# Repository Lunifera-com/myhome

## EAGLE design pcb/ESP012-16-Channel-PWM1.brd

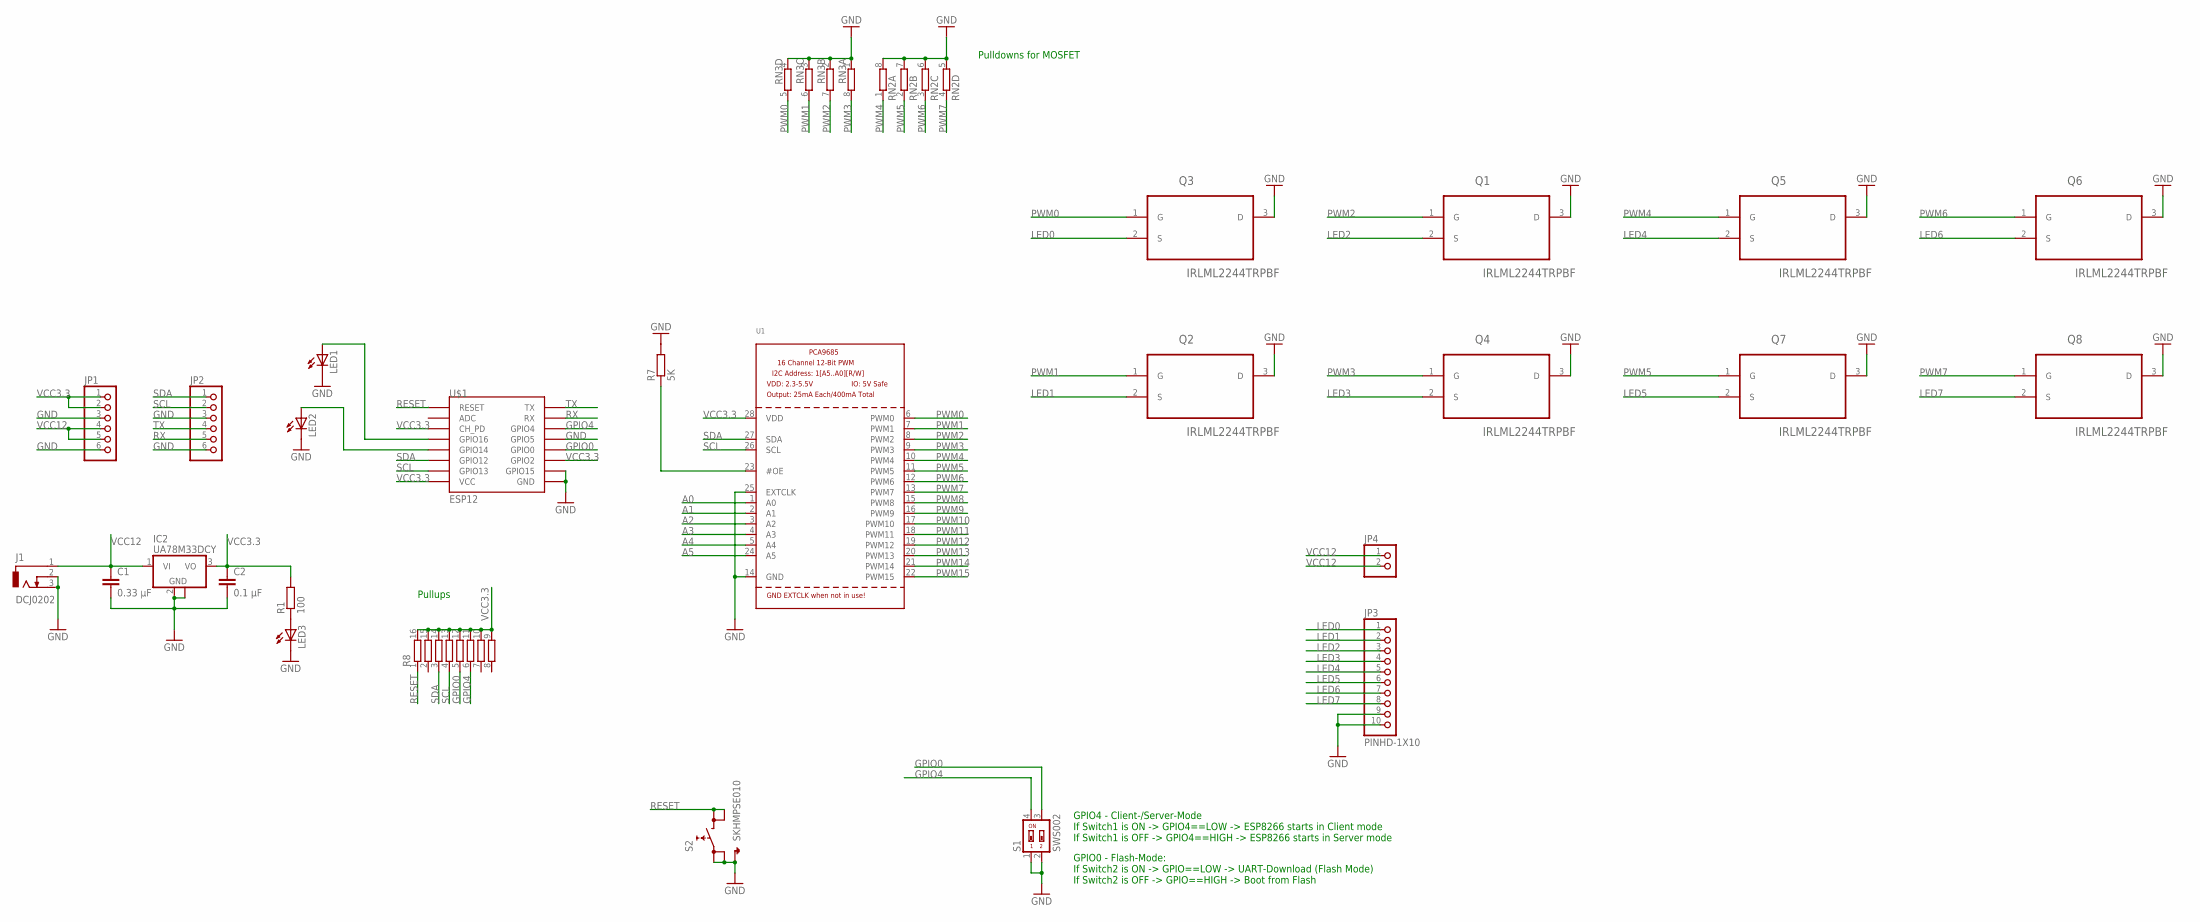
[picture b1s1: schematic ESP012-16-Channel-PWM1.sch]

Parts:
C1: 0.33 µF; C025-024X044
C2: 0.1 µF; C025-024X044
IC2: UA78M33DCY; SOT223
J1: DCJ0202
JP1, JP2: PINHD-1X6; 1X06
JP3: PINHD-1X10; 1X10-BIG
JP4: PINHD-1X2; 1X02
LED1, LED2, LED3: LEDCHIP-LED0805; CHIP-LED0805
Q1, Q2, Q3, Q4, Q5, Q6, Q7, Q8: IRLML2244TRPBF; SOT95P237X112-3N
R1: 100; MINI_MELF-0207R
R7: 5K; MINI_MELF-0207R
R8: 2QSP16-8; 2QSP16
RN2, RN3: 4R-NEXBS8V; EXBS8V
S1: SWS002; SMS-002
S2: SKHMPSE010; SKHMPXE010
U1: PCA9685; TSSOP28
U$1: ESP12

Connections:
A0: U1.1 (A0)
A1: U1.2 (A1)
A2: U1.3 (A2)
A3: U1.4 (A3)
A4: U1.5 (A4)
A5: U1.24 (A5)
GND: C1.2, C2.2, IC2.2 (GND), IC2.4 (GND), J1.2, J1.3, JP1.3, JP1.6, JP2.3, JP2.6, JP3.9, JP3.10, LED1.C, LED2.C, LED3.C, Q1.3 (D), Q2.3 (D), Q3.3 (D), Q4.3 (D), Q5.3 (D), Q6.3 (D), Q7.3 (D), Q8.3 (D), R7.2, RN2.5 (2), RN2.6 (2), RN2.7 (2), RN2.8 (2), RN3.1, RN3.2 (1), RN3.3 (1), RN3.4 (1), S1.1, S1.2, S2.1 (1.1), S2.2 (1.2), S2.5 (SH), U1.14 (GND), U1.25 (EXTCLK), U$1.GND, U$1.GPIO5, U$1.GPIO15
GPIO0: R8.5, S1.3, U$1.GPIO0
GPIO4: R8.6, S1.4, U$1.GPIO4
LED0: JP3.1, Q3.2 (S)
LED1: JP3.2, Q2.2 (S)
LED2: JP3.3, Q1.2 (S)
LED3: JP3.4, Q4.2 (S)
LED4: JP3.5, Q5.2 (S)
LED5: JP3.6, Q7.2 (S)
LED6: JP3.7, Q6.2 (S)
LED7: JP3.8, Q8.2 (S)
unnamed: R7.1, U1.23 (#OE)
PWM0: Q3.1 (G), RN3.5 (2), U1.6 (PWM0)
PWM1: Q2.1 (G), RN3.6 (2), U1.7 (PWM1)
PWM2: Q1.1 (G), RN3.7 (2), U1.8 (PWM2)
PWM3: Q4.1 (G), RN3.8 (2), U1.9 (PWM3)
PWM4: Q5.1 (G), RN2.1, U1.10 (PWM4)
PWM5: Q7.1 (G), RN2.2 (1), U1.11 (PWM5)
PWM6: Q6.1 (G), RN2.3 (1), U1.12 (PWM6)
PWM7: Q8.1 (G), RN2.4 (1), U1.13 (PWM7)
PWM8: U1.15 (PWM8)
PWM9: U1.16 (PWM9)
PWM10: U1.17 (PWM10)
PWM11: U1.18 (PWM11)
PWM12: U1.19 (PWM12)
PWM13: U1.20 (PWM13)
PWM14: U1.21 (PWM14)
PWM15: U1.22 (PWM15)
RESET: R8.1, S2.3 (2.1), S2.4 (2.2), U$1.RESET
RX: JP2.5, U$1.RX
S$1: LED1.A, U$1.GPIO16
S$2: LED2.A, U$1.GPIO14
SCL: JP2.2, R8.4, U1.26 (SCL), U$1.GPIO13
SDA: JP2.1, R8.3, U1.27 (SDA), U$1.GPIO12
TX: JP2.4, U$1.TX
VCC12: C1.1, IC2.1 (VI), J1.1, JP1.4, JP1.5, JP4.1, JP4.2

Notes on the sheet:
GPIO4 - Client-/Server-Mode If Switch1 is ON -> GPIO4==LOW -> ESP8266 starts in Client mode If Switch1 is OFF -> GPIO4==HIGH -> ESP8266 starts in Server mode
GPIO0 - Flash-Mode: If Switch2 is ON -> GPIO==LOW -> UART-Download (Flash Mode) If Switch2 is OFF -> GPIO==HIGH -> Boot from Flash
Pullups
Pulldowns for MOSFET

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
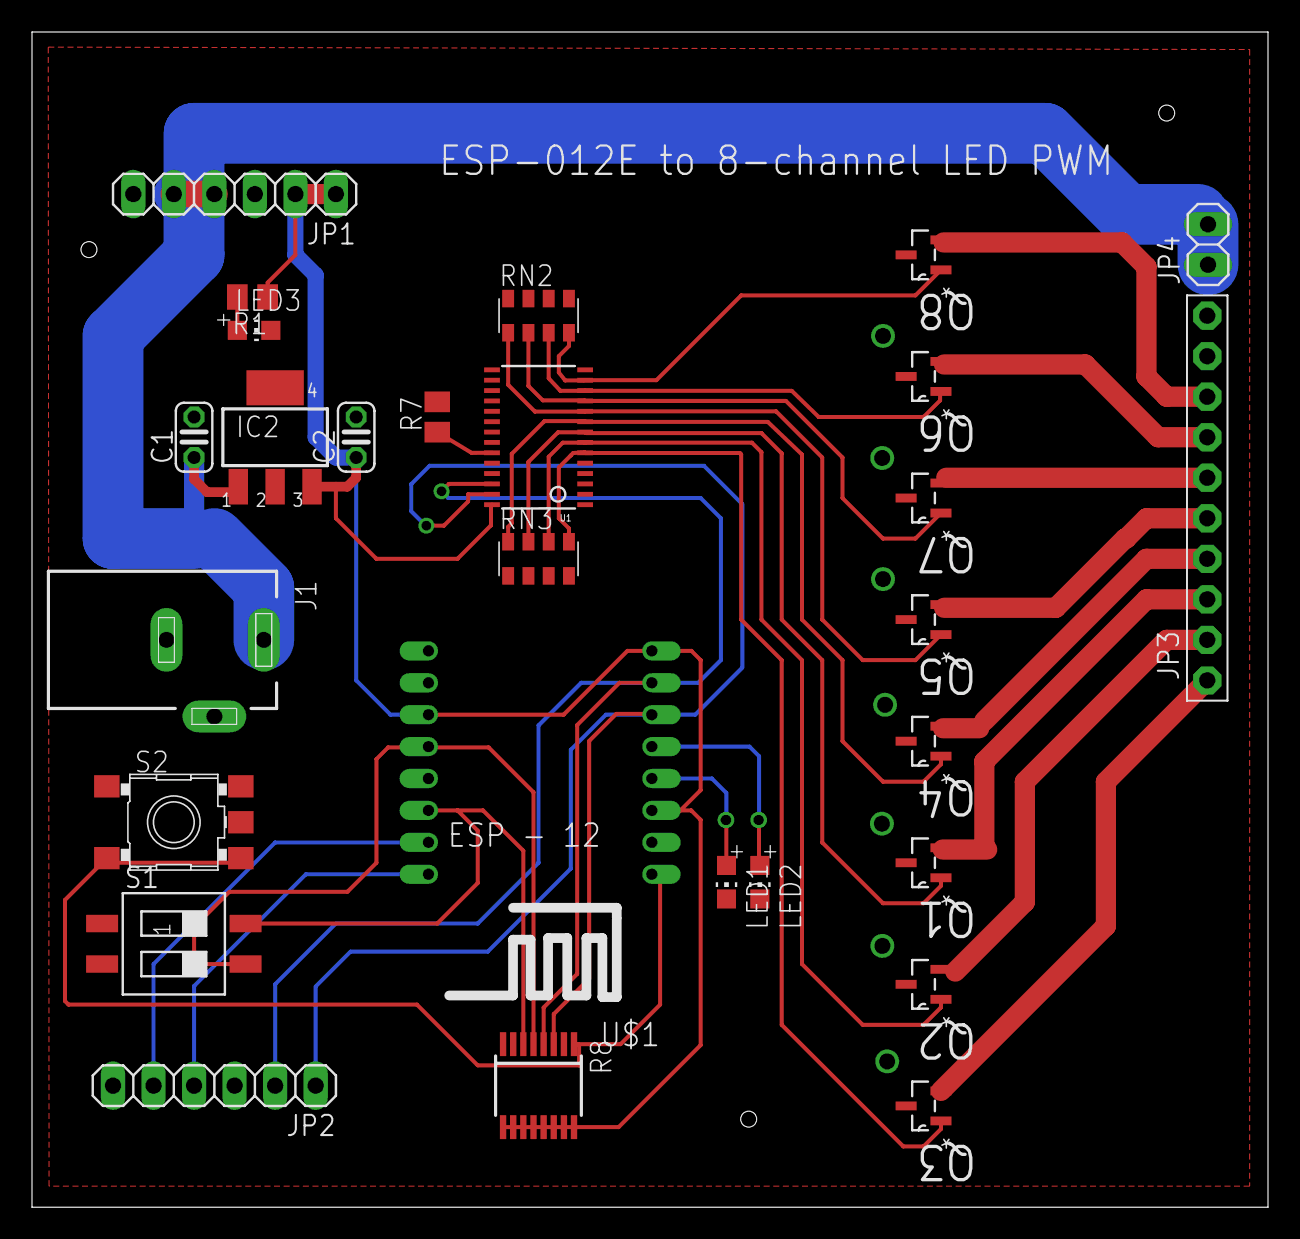
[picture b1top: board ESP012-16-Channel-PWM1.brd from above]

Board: 2 copper layers, 77.5 x 73.7 mm, 28 parts (0 on the bottom side), 30 nets.

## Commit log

2016-01-06 Initial commit of android application w/ working JSON reads
2016-01-06 added pcb layouts under the creative commons license
2016-01-07 changed 12V supply for LEDs to thicker wire
